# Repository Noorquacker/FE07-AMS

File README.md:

# FE07-AMS_Master

Wiki Link: http://cortex.device.mst.edu/mediawiki/index.php/Accumulator_Management_System(AMS)

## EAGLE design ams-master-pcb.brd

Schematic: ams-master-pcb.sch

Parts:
C1, C2, C4, C6, C7, C8, C9, C10, C11, C13, C15, C16, C17, C18, C19, C20, C21, C22, C23, C24, C25, C26, C27, C32, C33, C34, C35, C36, C37, C39, C41, C42, C43, C46, C47, C48, C49, C53, C54, C56, C75, C76, C77, C78, C87, C88, C89, C90, C91, C92, C95: 0.1uF; C0603K; PARTNO GRM188R71E104KA01D
C3, C93: DNP; C0603K
C5, C12, C14, C28, C31, C64, C65, C79, C80, C81: 4.7uF; C0603K; PARTNO GRM188R61A475KE15D
C38, C55, C70, C72, C99, C100: 10uF; C0603K; PARTNO GRM188R61A106KE69D
C40, C71: 4.7uF; C0603K; PARTNO GRM188R61E475KE11D
C50, C51: 22pF; C0603K; PARTNO C1608C0G1H220J080AA
C52: 1uF; C0603K; PARTNO GRM188R61E105KA12D
C82: 0.012uF; C0603K; PARTNO GRM188R71H123KA01D
C94: 9pF; C0603K; PARTNO GRM1885C1H9R0DA01D
C96, C97: 4.7uF 50v; C1206; PARTNO GRM31CR71H475KA12L
C98: 47uF; C1206; PARTNO GRM31CR61A476ME15L
D1: MM3Z12VB; SOD323F; PARTNO MM3Z12VB
D2, D3, D4, D5, D6, D8, D13: BAV21W; PARTNO BAV21WS-TP
D7: 50WQ10FNPBF; DPAK; PARTNO VS-50WQ10FNPBF
D11: MM3Z18VT1G; SOD-323; PARTNO MM3Z18VT1G
D17: ES1D; PARTNO ES1D
D18, D19: CMZ5928B; CMZ59; PARTNO CMZ5928B TR13
F1: 0458005.DR; FUSE_GENERIC_1206; PARTNO 0458005.DR
F2, F3: 0485001.DR; LITTELFUSE_485; PARTNO 0485001.DR
H1, H6, H7: 502443-0470; MOLEX_5024430470; PARTNO 5024430470
H2: MOUNT-HOLE-NPTH3.8MM; MOUNT-HOLE-3.8MM-NPTH
H4: 502443-0870; MOLEX_5024430870; PARTNO 5024430870
H16: MUSB2D11004BP; EMPTY_FOOTPRINT; PARTNO MUSB2D11004BP
J1: M50-3601042; SAMTEC-FTR-DUALROW; PARTNO M50-3601042
J2: TE-776087; PARTNO 776087-1
J3: MUSBD11130; MUSBD111XX; PARTNO MUSBD11130
J4, J6: MOLEX_43650-0416MOLEX_43650-0416_0_0; MOLEX_43650-0416_0
J7: 43650-0616; MOLEX_43650-0616
JP1, JP2, JP3, JP4, JP6, JP7: 0R; 0603-TWO-WAY-JUMPER; PARTNO ERJ-3EKF1002V
JP5: PINHD-1X8/90; 1X08/90
JP12: 10k; 0603-TWO-WAY-JUMPER; PARTNO ERJ-3EKF1002V
L1: 10uH; WURTH-744325XXXX; PARTNO 7443251000
L4: 220R @ 100M; 0805; PARTNO BLM21PG221SN1D
L5, L6: 2.2uH; 0805; PARTNO 74479775222
LED1: BLUE; CHIP-LED0805; PARTNO 5988110107F
LED2, LED3, LED6, LED7, LED8, LED9, LED14, LED15, LED16: GREEN; CHIP-LED0805; PARTNO 598-8170-107F
LED4, LED11, LED12: RED; CHIP-LED0805; PARTNO 5988110107F
LED5, LED10, LED13: ORANGE; CHIP-LED0805; PARTNO 598-8130-107F
MP1, MP2: MOUNT-HOLE3.8MM; MOUNT-HOLE-3.8MM
Q1: STD45P4LLF6AG; PARTNO STD45P4LLF6AG
Q2, Q3, Q4, Q5, Q6: BSS138; PARTNO BSS138
Q7, Q8: FQD3P50; PARTNO FQD3P50TM
R1, R2: 120; R0603; PARTNO ERJ-3EKF1200V
R3, R6, R26, R27, R28, R30, R36, R41, R42, R43, R44, R45, R46: 1k; R0603; PARTNO ERJ-3EKF1001V
R4, R11, R18, R19, R20, R21, R22, R23, R24, R64, R65, R102, R107: 10k; R0603; PARTNO ERJ-3EKF1002V
R5, R57: 1.5k; R0603; PARTNO ERJ-3EKF1501V
R7, R8: 270; R0603; PARTNO ERJ-3EKF2700V
R9, R10: 24R; R0603; PARTNO ERJ-3EKF24R0V
R12, R13, R14, R15, R16, R25: DNP/10k; R0603
R17: 100k; R0603; PARTNO ERJ-3EKF1002V
R29, R33, R98, R99, R100, R101, R103, R104, R105, R106: 150k; R0805; PARTNO ERJ-6ENF1503V
R31: 100; R0603; PARTNO ERJ-3EKF1000V
R32, R35: 2.2K; R0603; PARTNO ERJ-3EKF2201V
R47: 162k; R0603; PARTNO ERJ-3EKF1623V
R48: 15k; R0603; PARTNO ERJ-3EKF1502V
R50: 60.4k; R0603; PARTNO ERJ-3EKF6042V
R51: 11.5k; R0603; PARTNO ERJ-3EKF1152V
R52, R53: DNP; R0603; PARTNO *
R62, R63: 20k; R0603; PARTNO ERJ-3EKF2002V
R72, R81: 2.2k; R0603; PARTNO ERJ-3EKF2201V
R96, R97: 0R; R0603; PARTNO ERJ-3GEY0R00V
R108, R109: 1M; R0805; PARTNO ERJ-6ENF1004V
S2: 147873-2; TE-147873-2; PARTNO 147873-2
U1, U32, U35: PDS1-S5-S5-M-TR; PDS1-M; PARTNO PDS1-S5-S5-M-TR
U2: SN74LVC1G32DBV; SOT23-5; PARTNO SN74LVC1G32DBVR
U3: SN74LVC1G08DBV; SOT23-5; PARTNO SN74LVC1G08DBVR
U4: RM46L852; LQFP144
U5, U6: CD4050BD; SOIC-16; PARTNO CD4050BDR
U7, U13: MCP2562FD; SOIC8-N_MC; PARTNO MCP2562FD-E/SN
U8: ADUM3160BRWZ-RL; ADUM3160; PARTNO ADUM3160BRWZ-RL
U10, U11, U30, U31, U33, U34: ISO7221; ISO722X; PARTNO ISO7221CDR
U14: SN74LVC541A; TSSOP20_MC; PARTNO SN74LVC541APWR
U16: LM3671MF-3.3/NOPB; SOT23-5; PARTNO LM3671MF-3.3/NOPB
U17: SN74LVC1G02DBV; SOT23-5; PARTNO SN74LVC1G02DBVR
U18: LM3671MF-1.2/NOPB; SOT23-5; PARTNO LM3671MF-1.2/NOPB
U22, U23: FAN3214; PARTNO FAN3214TMX
U24, U25, U27: CSD17506Q5A; SON_5X6; PARTNO CSD17506Q5A
U36, U37: ADC121S021; PARTNO ADC121S021CIMF/NOPB
U38: FT232RL; SSOP28; PARTNO FT232RL-REEL
U42: TPS54540DDARQ1; TPS54540; PARTNO TPS54540DDAR
Y2: 16MHz; CSM-3X; PARTNO ECS-160-20-3X-TR

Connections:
5KW_3V3: JP5.3, Q5.S, R11.1, U4.133 (GIOB[1]/USB1.PORTPOWER), U14.2 (IN)
5KW_GLV: D6.CATHODE, J2.P$1 (P1), R16.2
5VREG_EN1: R52.1, R53.2, U42.3 (EN)
+1V2: C33.1, C34.1, C35.1, C36.1, C37.1, C39.1, C41.1, C43.1, C47.1, C49.1, C53.1, C55.1, C72.1, L6.2, U4.17 (VCC), U4.29 (VCC), U4.45 (VCC), U4.48 (VCC), U4.49 (VCC), U4.57 (VCC), U4.87 (VCC), U4.101 (VCC), U4.114 (VCC), U4.123 (VCC), U4.137 (VCC), U4.143 (VCC), U18.4 (FB)
+3V3: C1.1, C2.1, C7.1, C10.1, C13.1, C15.1, C16.1, C21.1, C22.1, C23.1, C27.1, C38.1, C42.1, C46.1, C48.1, C54.1, C56.1, C70.1, C75.1, C76.1, C77.1, C78.1, H6.3, H7.3, J1.5, JP5.6, L4.1, L5.2, LED2.A, LED5.A, LED11.A, LED12.A, LED13.A, Q2.G, Q3.G, Q4.G, Q5.G, Q6.G, R21.1, R22.1, R32.1, R35.1, U2.5 (VCC), U3.5 (VCC), U4.10 (VCCIO), U4.26 (VCCIO), U4.42 (VCCIO), U4.69 (VCCAD), U4.104 (VCCIO), U4.120 (VCCIO), U4.134 (VCCP), U4.136 (VCCIO), U5.1 (VCC), U7.5 (SPLIT/VIO), U8.12 (PIN), U8.13 (SPD), U8.14 (VDD2), U8.16 (VBUS2), U10.P$8 (VCC2), U11.P$8 (VCC2), U14.20 (VCC), U16.4 (FB), U17.5 (VCC), U30.P$8 (VCC2), U31.P$8 (VCC2), U33.P$8 (VCC2), U34.P$8 (VCC2), U38.4 (VCCIO), U38.19 (!RESET)
+5V: C6.1, C11.1, C12.1, C14.1, C40.1, C71.1, C79.1, C80.1, C98.1, C99.1, C100.1, JP5.7, L1.P$2, LED3.A, R50.2, U1.2 (VIN), U7.3 (VDD), U16.1 (VIN), U16.3 (EN), U18.1 (VIN), U18.3 (EN), U32.2 (VIN), U35.2 (VIN), U38.20 (VCC)
+5V/1: C17.1, C18.1, C19.1, C20.1, C28.1, J7.4, LED16.A, U1.5 (+VO), U10.P$1 (VCC1), U11.P$1 (VCC1), U13.3 (VDD), U13.5 (SPLIT/VIO)
+5V/2: C81.1, C87.1, C88.1, C91.1, LED15.A, U30.P$1 (VCC1), U31.P$1 (VCC1), U31.P$3 (INB), U32.5 (+VO), U36.P$1 (VA)
+5V/3: C5.1, C89.1, C90.1, C92.1, LED14.A, U33.P$1 (VCC1), U34.P$1 (VCC1), U34.P$3 (INB), U35.5 (+VO), U37.P$1 (VA)
+15V: C24.1, C25.1, C26.1, C96.1, C97.1, D1.CATHODE, H4.2, JP5.8, JP12.3, Q1.S, R4.1, R17.1, R18.1, R19.1, R23.1, R52.2, R72.1, U6.1 (VCC), U22.6 (VCC), U23.6 (VCC), U42.2 (VIN)
BATTERY_VOLTAGE_FB: R96.1, R101.2, R102.1
BATTERY_VOLTAGE_IS_AVAILABLE: U4.40 (MIBSPI1NCS[2]/N2HET1[19]/MDIO), U34.P$6 (OUTB)
BATTERY_VOLTAGE_MONITOR_CS: U4.130 (MIBSPI1NCS[1]/N2HET1[17]/MII_COL/USB1.S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), U33.P$7 (INA)
BMS_CAN_RX: JP7.3, U4.129 (CAN2RX)
BMS_CAN_TX: JP6.3, U4.128 (CAN2TX)
BMS_FAULT: U4.2 (GIOA[0]/USB2.VP/USB_FUNC.RXDPI), U11.P$6 (OUTB)
BMS_FAULT_HV: J7.5, U11.P$3 (INB)
BMS_RX: JP7.2, U10.P$6 (OUTB)
BMS_RX_HV: J7.2, JP3.2
BMS_TX: JP6.2, U11.P$7 (INA)
BMS_TX_HV: J7.3, JP4.2
BMS_UART_RX: JP7.1, U4.38 (N2HET1[6]/SCIRX/EPWM5A)
BMS_UART_TX: JP6.1, U4.39 (N2HET1[13]/SCITX/EPWM5B)
BOOT_5V2: C95.1, U42.1 (BOOT)
CAR_CAN_N: J2.P$7 (P7), R2.1, U7.6 (CANL)
CAR_CAN_P: J2.P$8 (P8), R2.2, U7.7 (CANH)
CAR_CAN_P1: JP2.2, U11.P$2 (OUTA)
CAR_CAN_RX: U4.90 (CAN1RX), U7.4 (RXD)
CAR_CAN_TX: U4.89 (CAN1TX), U7.1 (TXD)
COMP_5V2: C94.1, R48.2, U42.6 (COMP)
CONTACTOR_CLOSED_3V3: Q4.S, R22.2, U4.22 (GIOA[7]/N2HET2[6]/EPWM2A), U17.4 (OUT)
CONTACTOR_CLOSED_GLV: D4.CATHODE, J2.P$6 (P6), R14.2
CONTACTOR_OPEN_3V3: Q3.S, R21.2, U3.4 (OUT), U4.16 (GIOA[6]/N2HET2[4]/EPWM1B)
CONTACTOR_OPEN_GLV: D3.CATHODE, J2.P$5 (P5), R13.2
CURRENT_SENSE_-75_TO_75A: JP5.4, U4.73 (AD1IN[2])
CURRENT_SENSE_-750_TO_750A: JP5.5, U4.74 (AD1IN[3])
CURRENT_SHORT_3V3: JP5.2, Q6.S, R24.1, U4.142 (GIOB[2])
CURRENT_SHORT_GLV: D8.CATHODE, J2.P$9 (P9), R25.2
FAULT_AMS_GLV: D2.CATHODE, J2.P$3 (P3), R12.2
FAULT_AMS_INDICATOR: Q2.S, R20.2, U4.126 (GIOB[0]/USB1.TXDAT), U14.3 (IN)
FAULT_IMD_3V3: U4.14 (GIOA[5]/EXTCLKIN/EPWM1A/N2HET1_PIN_NDIS), U5.4 (OUT), U14.9 (IN)
FAULT_IMD_GLV: D5.CATHODE, J2.P$2 (P2), R15.2
FAULT_IMD_PRE-BUFFER: H4.8, R81.1, U5.5 (IN), U6.14 (IN)
FB_5V2: R50.1, R51.2, U42.5 (FB)
FILTERED_BATTERY_VOLTAGE_FB: C93.1, R96.2, U36.P$3 (VIN)
FILTERED_VEHICLE_VOLTAGE_FB: C3.1, R97.2, U37.P$3 (VIN)
GND: C1.2, C2.2, C4.2, C6.2, C7.2, C10.2, C11.2, C12.2, C13.2, C14.2, C15.2, C16.2, C21.2, C22.2, C23.2, C24.2, C25.2, C26.2, C27.2, C31.2, C32.2, C33.2, C34.2, C35.2, C36.2, C37.2, C38.2, C39.2, C40.2, C41.2, C42.2, C43.2, C46.2, C47.2, C48.2, C49.2, C52.2, C53.2, C54.2, C55.2, C56.2, C64.2, C65.2, C70.2, C71.2, C72.2, C75.2, C76.2, C77.2, C78.2, C79.2, C80.2, C82.2, C94.2, C96.2, C97.2, C98.2, C99.2, C100.2, D7.1 (ANODE), D7.3 (ANODE), D11.ANODE, H4.1, H4.3, J1.4, J1.8, J1.10, J1.12, J1.16, J1.20, J2.P$21 (P21), JP5.1, JP12.1, LED1.C, LED6.C, LED7.C, LED8.C, LED9.C, LED10.C, MP1.P$1, MP2.P$1, R5.1, R11.2, R12.1, R13.1, R14.1, R15.1, R16.1, R20.1, R24.2, R25.1, R30.1, R36.1, R47.1, R51.1, R53.1, R64.1, R65.1, R81.2, S2.P$2 (2), U1.1 (GND), U2.3 (GND), U3.3 (GND), U4.11 (VSS), U4.21 (VSS), U4.27 (VSS), U4.28 (VSS), U4.34 (TEST), U4.43 (VSS), U4.44 (VSS), U4.47 (VSS), U4.50 (VSS), U4.56 (VSS), U4.67 (ADREFLO), U4.68 (VSSAD), U4.88 (VSS), U4.102 (VSS), U4.103 (VSS), U4.115 (VSS), U4.121 (VSS), U4.122 (VSS), U4.135 (VSS), U4.138 (VSS), U4.144 (VSS), U5.8 (GND), U6.8 (GND), U7.2 (VSS), U7.8 (STBY), U8.9 (GND2), U8.15 (GND2), U10.P$5 (GND2), U11.P$5 (GND2), U14.1 (!E), U14.10 (GND), U14.19 (!E), U16.2 (GND), U17.3 (GND), U18.2 (GND), U22.3 (GND), U23.3 (GND), U24.1 (S), U24.2 (S), U24.3 (S), U25.1 (S), U25.2 (S), U25.3 (S), U27.1 (S), U27.2 (S), U27.3 (S), U30.P$5 (GND2), U31.P$5 (GND2), U32.1 (GND), U33.P$5 (GND2), U34.P$5 (GND2), U35.1 (GND), U38.7 (GND), U38.18 (GND), U38.21 (GND), U38.25 (GND), U38.26 (TEST), U42.7 (GND), U42.PAD (GND), U42.PAD1 (GND)
GND1: C17.2, C18.2, C19.2, C20.2, C28.2, J7.6, R28.1, U1.4 (0V), U10.P$4 (GND1), U11.P$4 (GND1), U13.2 (VSS), U13.8 (STBY)
GND2: C81.2, C87.2, C88.2, C91.2, C93.2, J4.3, J4.4, R27.1, R102.2, R108.1, U30.P$4 (GND1), U31.P$4 (GND1), U32.4 (0V), U36.P$2 (GND)
GND3: C3.2, C5.2, C89.2, C90.2, C92.2, J6.3, J6.4, R26.1, R107.2, R109.1, U33.P$4 (GND1), U34.P$4 (GND1), U35.4 (0V), U37.P$2 (GND)
HV_BMS_CAN_N: JP3.3, R1.1, U13.6 (CANL)
HV_BMS_CAN_P: JP4.3, R1.2, U13.7 (CANH)
HV_BMS_CAN_RX: JP1.3, U13.4 (RXD)
HV_BMS_CAN_TX: JP2.3, U13.1 (TXD)
IMD_GND: H4.4, J2.P$4 (P4)
IMD_PWM_OUT_3V3: U4.30 (N2HET1[2]/SPI4SIMO[0]/EPWM3A), U5.6 (OUT)
INDICATOR_1: U4.125 (N2HET1[14]/USB1.TXSE0), U14.8 (IN)
INDICATOR_2: U4.124 (N2HET1[12]/MII_CRS/RMII_CRS_DV), U14.7 (IN)
JTAG_RESET: J1.15, U4.46 (NPORRST)
MCU_RESET1: C52.1, R31.1, R32.2, U4.116 (NRST)
M_LS: H4.6, R72.2, U5.7 (IN)
unnamed: D3.ANODE, U6.10 (OUT)
unnamed: R41.1, U14.14 (OUT)
unnamed: LED6.A, R41.2
unnamed: R42.1, U14.15 (OUT)
unnamed: R45.1, U14.13 (OUT)
unnamed: Q3.D, R18.2, U6.9 (IN)
unnamed: D11.CATHODE, R57.2, U5.3 (IN)
unnamed: Q4.D, R19.2, U6.7 (IN)
unnamed: R46.2, U14.17 (OUT)
unnamed: D5.ANODE, U6.15 (OUT)
unnamed: C82.1, R48.1
unnamed: LED7.A, R42.2
unnamed: R43.1, U14.16 (OUT)
unnamed: R3.2, U14.11 (OUT)
unnamed: LED11.C, R46.1
unnamed: LED12.C, R3.1
unnamed: R8.1, U38.22 (CBUS1)
unnamed: R6.1, U14.18 (OUT)
unnamed: LED1.A, R6.2
unnamed: LED5.C, R7.2
unnamed: LED13.C, R8.2
unnamed: C4.1, U38.17 (3V3OUT)
unnamed: C9.1, U8.3 (VDD1), U8.4 (PDEN), U8.5 (SPU)
unnamed: F1.P$2, J2.P$16 (P16)
unnamed: JP1.2, U10.P$3 (INB)
unnamed: JP1.1, JP3.1
unnamed: JP2.1, JP4.1
unnamed: Q5.D, R4.2, U6.5 (IN)
unnamed: D6.ANODE, U6.4 (OUT)
unnamed: Q6.D, R23.2, U6.3 (IN)
unnamed: D8.ANODE, U6.2 (OUT)
unnamed: LED8.A, R43.2
unnamed: LED9.A, R44.2
unnamed: LED10.A, R45.2
unnamed: LED14.C, R26.2
unnamed: LED15.C, R27.2
unnamed: LED16.C, R28.2
unnamed: R29.2, R98.1
unnamed: LED3.C, R30.2
unnamed: U2.4 (OUT), U3.2 (IN2), U17.2 (IN2)
unnamed: R33.2, R103.1
unnamed: D2.ANODE, U6.12 (OUT)
unnamed: LED4.A, R35.2
unnamed: D4.ANODE, U6.6 (OUT)
unnamed: R44.1, U14.12 (OUT)
unnamed: LED2.C, R36.2
unnamed: L5.1, U16.5 (SW)
unnamed: R7.1, U38.23 (CBUS0)
unnamed: L6.1, U18.5 (SW)
unnamed: C50.1, U4.18 (OSCIN), Y2.P$1
unnamed: C51.1, U4.20 (OSCOUT), Y2.P$2
unnamed: R31.2, S2.P$1 (1)
unnamed: C50.2, C51.2, U4.19 (KELVIN_GND)
unnamed: LED4.C, U4.117 (NERROR)
unnamed: R9.2, U8.6 (UD-)
unnamed: R10.2, U8.7 (UD+)
unnamed: D13.CATHODE, JP12.2, R57.1
unnamed: Q2.D, R17.2, U6.11 (IN)
unnamed: R98.2, R99.1
unnamed: R99.2, R100.1
unnamed: R100.2, R101.1
unnamed: U31.P$2 (OUTA), U36.P$4 (SCLK)
unnamed: U30.P$3 (INB), U36.P$5 (SDATA)
unnamed: U30.P$2 (OUTA), U36.P$6 (!CS)
unnamed: U34.P$2 (OUTA), U37.P$4 (SCLK)
unnamed: D1.ANODE, Q1.G, R5.2
unnamed: F1.P$1, Q1.D
unnamed: D18.2 (ANODE), Q7.G, R108.2
unnamed: F2.P$2, Q7.D
unnamed: F2.P$1, J4.1, J4.2
unnamed: U33.P$3 (INB), U37.P$5 (SDATA)
unnamed: U33.P$2 (OUTA), U37.P$6 (!CS)
unnamed: R103.2, R104.1
unnamed: R104.2, R105.1
unnamed: R105.2, R106.1
unnamed: D19.2 (ANODE), Q8.G, R109.2
unnamed: F3.P$2, J6.2, Q8.D
unnamed: F3.P$1, J6.1
unnamed: D19.1 (CATHODE), Q8.S, R33.1
unnamed: D18.1 (CATHODE), Q7.S, R29.1
NEGATIVE_CONTACTOR_CTRL: U4.140 (N2HET1[18]/EPWM6A), U14.5 (IN), U22.4 (IN)
NEG_CONTACTOR_SENSE: H7.4, R63.2, R65.2
NEG_CONTACTOR_SENSE_FILTERED: C65.1, R63.1, U3.1 (IN1), U4.5 (GIOA[1]/USB2.VM/USB_FUNC.RXDMI), U17.1 (IN1)
NEG_FET: H7.2, U25.5 (D), U25.6 (D), U25.7 (D), U25.8 (D), U25.PAD (D), U25.PAD1 (D), U25.VIA1 (D), U25.VIA2 (D), U25.VIA3 (D), U25.VIA4 (D), U25.VIA5 (D), U25.VIA6 (D), U25.VIA7 (D), U25.VIA8 (D), U25.VIA9 (D)
NEG_GATE: U22.5 (OUT), U25.4 (G)
NTRST: J1.2, U4.109 (NTRST)
POSITIVE_CONTACTOR_CTRL: U4.141 (N2HET1[20]/EPWM6B), U14.6 (IN), U22.2 (IN)
POS_CONTACTOR_SENSE: H6.4, R62.2, R64.2
POS_CONTACTOR_SENSE_FILTERED: C64.1, R62.1, U2.1 (IN1), U4.9 (GIOA[2]/USB2.TXDAT/USB_FUNC.TXDO/N2HET2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)
POS_FET: H6.2, U24.5 (D), U24.6 (D), U24.7 (D), U24.8 (D), U24.PAD (D), U24.PAD1 (D), U24.VIA1 (D), U24.VIA2 (D), U24.VIA3 (D), U24.VIA4 (D), U24.VIA5 (D), U24.VIA6 (D), U24.VIA7 (D), U24.VIA8 (D), U24.VIA9 (D)
POS_GATE: U22.7 (OUT), U24.4 (G)
PRECHARGE_CONTACTOR_CTRL: U2.2 (IN2), U4.139 (N2HET1[16]/EPWM1SYNCI/EPWM1SYNCO), U14.4 (IN), U23.2 (IN)
PRECH_GATE: U23.7 (OUT), U27.4 (G)
PRE_FET: D17.2 (ANODE), H1.2, U27.5 (D), U27.6 (D), U27.7 (D), U27.8 (D), U27.PAD (D), U27.PAD1 (D), U27.VIA1 (D), U27.VIA2 (D), U27.VIA3 (D), U27.VIA4 (D), U27.VIA5 (D), U27.VIA6 (D), U27.VIA7 (D), U27.VIA8 (D), U27.VIA9 (D)
RTCK: J1.9, U4.113 (RTCK)
RT_5V2: R47.2, U42.4 (RT/CLK)
SC_FROM_OUTSIDE_SENSE: U4.36 (N2HET1[4]/EPWM4B), U4.37 (MIBSPI3NCS[1]/N2HET1[25]/MDCLK), U5.2 (OUT)
SHUTDOWN_CIRCUIT_FROM_OUTSIDE: D13.ANODE, D17.1 (CATHODE), H1.1, H6.1, H7.1, J2.P$23 (P23)
SW_5V2: C95.2, D7.2 (CATHODE), L1.P$1, U42.8 (SW)
TCK: J1.11, U4.112 (TCK)
TDI: J1.3, U4.110 (TDI)
TDO: J1.7, U4.111 (TDO)
TMS: J1.1, U4.108 (TMS)
UART_RX: U4.131 (LINRX), U38.1 (TXD)
UART_TX: U4.132 (LINTX), U38.5 (RXD)
USBISO_D_N: J3.2 (D-), R9.1
USBISO_D_P: J3.3 (D+), R10.1
USBISO_GND: C8.2, C9.2, J3.4 (GND), U8.2 (GND1), U8.8 (GND1)
USBISO_VCC: C8.1, J3.1 (VCC), U8.1 (VBUS1)
USB_D_N: U8.11 (DD-), U38.16 (USBDM)
USB_D_P: U8.10 (DD+), U38.15 (USBDP)
VCCAD: C31.1, C32.1, L4.2, U4.66 (ADREFHI)
VEHICLE_VOLTAGE_FB: R97.1, R106.2, R107.1
VEHICLE_VOLTAGE_IS_AVAILABLE: U4.93 (MIBSPI1SIMO[0]), U31.P$6 (OUTB)
VEHICLE_VOLTAGE_MONITOR_CS: U4.105 (MIBSPI1NCS[0]/MIBSPI1SOMI[1]/MII_TXD[2]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), U30.P$7 (INA)
VOLTAGE_MONITOR_MISO: U4.94 (MIBSPI1SOMI[0]), U30.P$6 (OUTB), U33.P$6 (OUTB)
VOLTAGE_MONITOR_SCLK: U4.95 (MIBSPI1CLK), U31.P$7 (INA), U34.P$7 (INA)
WAKEUP: U4.1 (GIOB[3]/USB2.RCV/USB_FUNC.RXDI), U10.P$7 (INA)
WAKEUP_HV: J7.1, U10.P$2 (OUTA)

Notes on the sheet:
MICROCONTROLLER
KEY
JTAG
Connector to interface with the wiring harness in the Grounded Low Voltage System
Reverse voltage protection
GLVS Connector
7443251000
+3v3 buck
74479775222
+1v2 buck
5V Regulator
3V3 Regulator
1V2 Regulator
CONTACTOR RELAYS
Low-side MOSFETs to control power to the battery contactors
(+) MAIN CONTACTOR POSITIVE
(-) MAIN CONTACTOR NEGATIVE
PRECHARGE CONTACTOR
The main contactors have a secondary coil which we use to detect if the contacts have welded shut. When the contact is closed, the sense pin will be shorted to 3v3. When the contact is open, the sense pin is pulled to GND by a 10k resistor. Logic 0 on CONTACTOR_OPEN indicates that at least one cont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
SHUTDOWN CIRCUIT
CONTACTOR STATE DETECTION
Connects to the low volt side of the IMD
IMD CONNECTOR
Level shift the logic up to GLV battery level. Buffer separates the GIO pin of the microcontroller from the GLV connector
Needs a 10k pulldown at receiver end
OUTPUT BUFFERS
ISOLATED DC-DC CONVERTER
CONNECTION TO TS BATTERY POSITIVE TERMINAL
CONNECTION TO TS BATTERY NEGATIVE TERMINAL
Connect to TS voltage inside the contactors
Connect to TS voltage outside the contactors
SOURCE 400v Connectors
CAN TRANSCEIVER
CAR CAN
BATTERY VOLTAGE CONNECTIONS
VEHICLE VOLTAGE CONNECTIONS
Indicator LEDs
Indicator LEDs show the status of the system IMD_FAULT and FAULT_AMS_INDCATOR are is an active low error (the signal is low when there is a fault) so it requires an extra MOSFET to invert the signal for the LEDs
Active low fault
Needs a 10k pulldown at receiver end

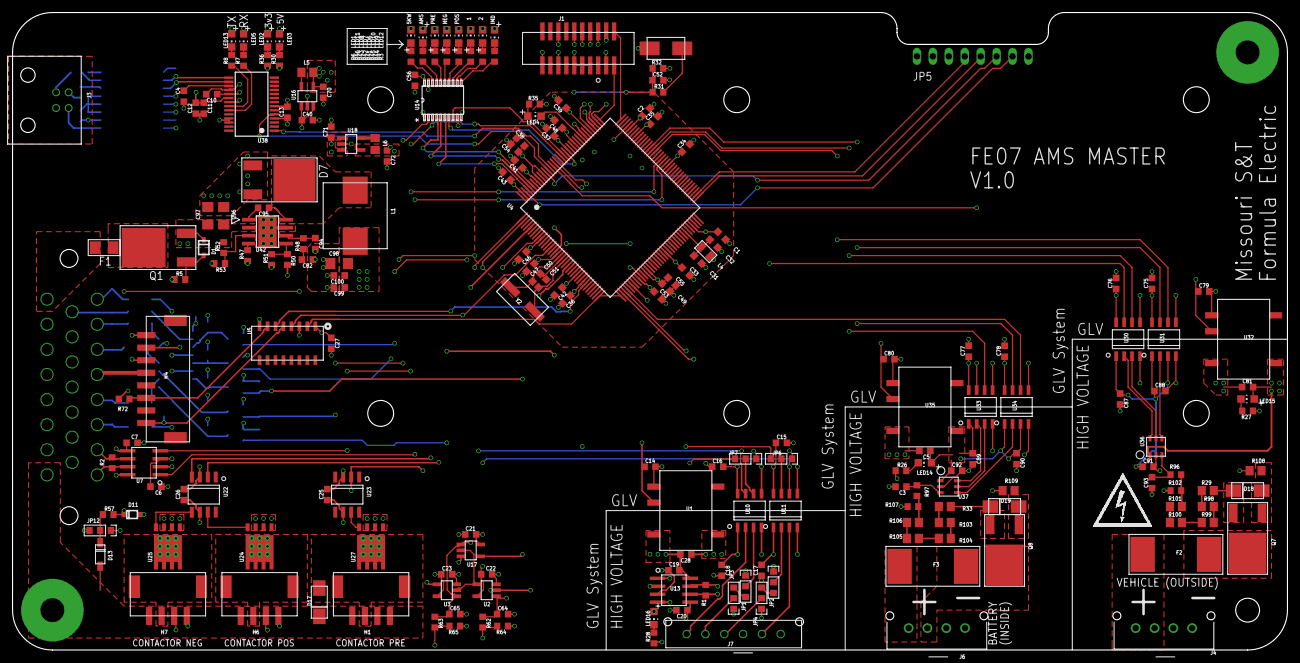
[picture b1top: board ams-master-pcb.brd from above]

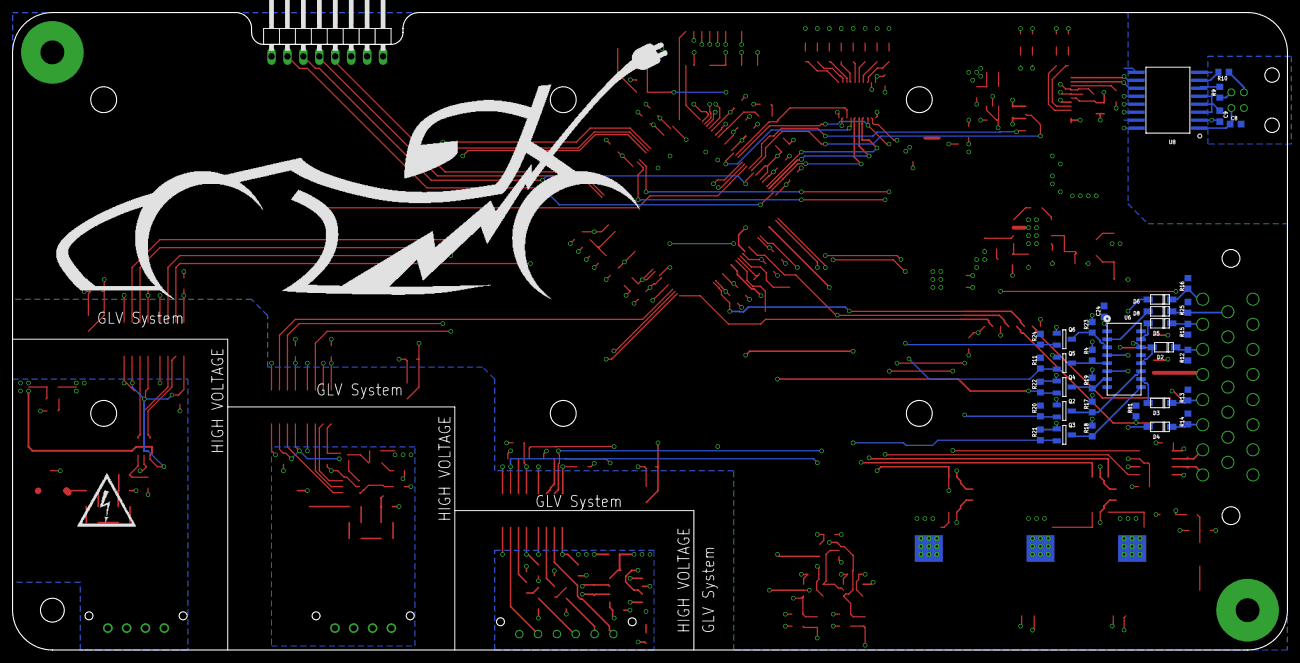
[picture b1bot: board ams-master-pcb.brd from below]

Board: 4 copper layers, 203.2 x 101.6 mm, 246 parts (36 on the bottom side), 180 nets.

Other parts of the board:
U$1: BENDER-ISOMETER

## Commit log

2020-09-02 Started New Schematic
2020-09-05 Started updating TS sections, moved SPI stuff. Needs to look a lot nicer still.
2020-09-07 Changed a bit of the Isolated Portion
2020-09-08 Adding Connections to Hercules
2020-09-12 Pinout on Hercules complete
2021-02-10 Almost done, need to work on HV sensing
    Need to source a connector, look at SPI comm with ADCs, design reveiw
2021-02-11 error with last push
2021-02-12 Push to work on laptop
2021-02-16 Output buffers
2021-02-16 Nearly done
2021-02-17 Schematic done, will begin routing
2021-02-17 Added some comments
2021-02-17 Started Routing
2021-02-27 Added some comments to the schematic, good talking points
2021-03-08 HV isolation, 5V supply
2021-03-10 rough
2021-03-10 routing
2021-03-11 Continued layout
2021-03-11 Fixed an overlap
2021-03-17 moving decoupling caps
2021-03-17 DRC time
2021-03-17 DRC passed
2021-03-17 silkscreen done
2021-03-17 CAM processed
2021-04-17 started coding
2021-04-17 SPI SUCKS :sunglasses:
2021-04-20 Test Code to Click Contactors :sunglasses:
2021-04-21 Mimicking MB
2021-04-22 Finished Input Functions, working on CAN
2021-04-22 Worked on CAN :)
2021-04-23 currently implementing uart for BMS, very early stages of that :sunglasses:
2021-04-24 ready to test bms communication
2021-04-24 still trying to figure out talking to BMS
2021-05-01 Writing custom BMS communication
2021-05-01 Almost done with BMS communication library, just need to add read data and init boards functions
2021-05-01 Added BMS Init Function, need to do read voltages still
2021-05-01 Added BMS Init Function, need to do read voltages still (++, off to bed :sleeping:)
2021-05-01 Wrote wakeup function, init is done, working on get bms data functions
2021-05-01 Ready to test BMS communication using custom library
2021-05-02 testing bms communication
2021-05-06 ready for battery charger demo
2021-05-08 Tested for RTS
2021-09-25 Added Kate IDE support (and possible vscode support, idk)
2021-09-25 include state machine diagrams and add missing header function to suppress warning
2021-09-26 started working on an actual diagram
